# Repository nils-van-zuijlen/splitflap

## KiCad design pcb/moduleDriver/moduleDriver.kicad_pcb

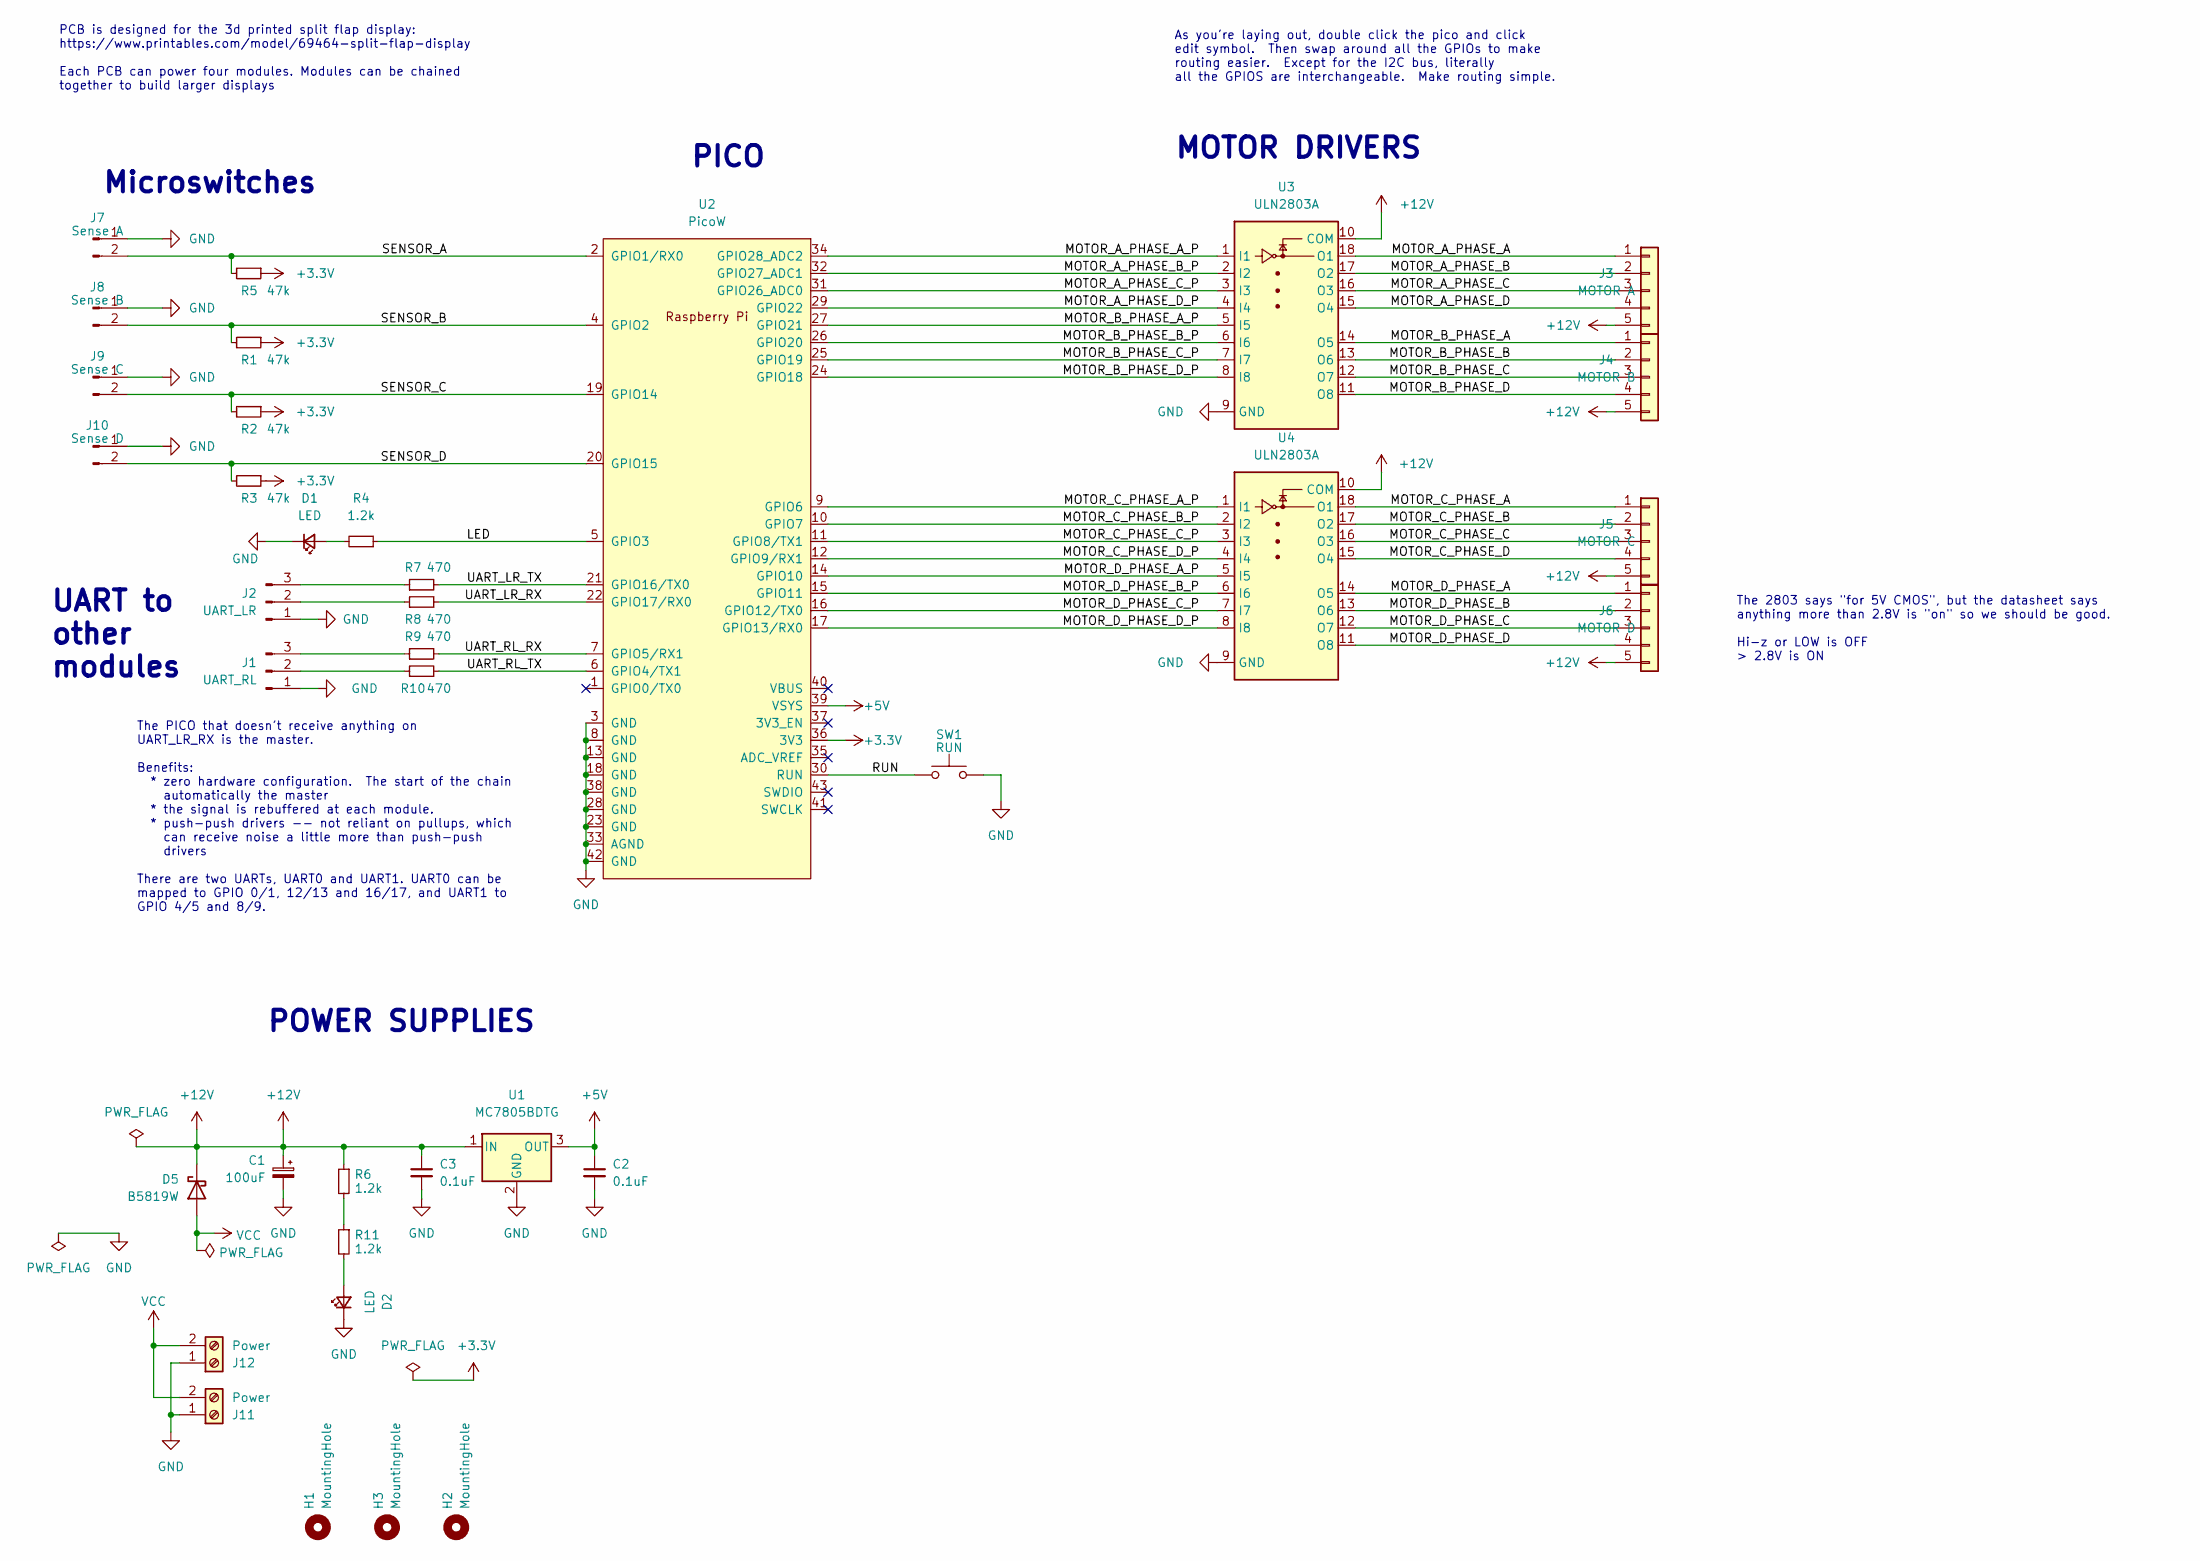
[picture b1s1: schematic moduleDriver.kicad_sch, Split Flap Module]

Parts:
C1: 100uF; CP_Elec_8x10; LCSC# C176665
C2, C3: 0.1uF; C_1206_3216Metric; LCSC# C14663
D1, D2: LED; LED_1206_3216Metric; LCSC# C72041
D5: B5819W; D_SOD-123; LCSC# C8598
H1, H2, H3: MountingHole; MountingHole_3.2mm_M3_ISO7380
J1: UART_RL; JST_XH_B3B-XH-A_1x03_P2.50mm_Vertical
J2: UART_LR; JST_XH_B3B-XH-A_1x03_P2.50mm_Vertical
J3: MOTOR A; JST_XH_B5B-XH-A_1x05_P2.50mm_Vertical
J4: MOTOR B; JST_XH_B5B-XH-A_1x05_P2.50mm_Vertical
J5: MOTOR C; JST_XH_B5B-XH-A_1x05_P2.50mm_Vertical
J6: MOTOR D; JST_XH_B5B-XH-A_1x05_P2.50mm_Vertical
J7: Sense A; JST_XH_B2B-XH-A_1x02_P2.50mm_Vertical
J8: Sense B; JST_XH_B2B-XH-A_1x02_P2.50mm_Vertical
J9: Sense C; JST_XH_B2B-XH-A_1x02_P2.50mm_Vertical
J10: Sense D; JST_XH_B2B-XH-A_1x02_P2.50mm_Vertical
J11, J12: Power; PhoenixContact_MSTBA_2,5_2-G_1x02_P5.00mm_Horizontal
R1, R2, R3, R5: 47k; R_1206_3216Metric; LCSC# C25819
R4, R6, R11: 1.2k; R_1206_3216Metric; LCSC# C22765
R7, R8, R9, R10: 470; R_1206_3216Metric; LCSC# C23179
SW1: RUN; SW_PUSH_6mm
U1: MC7805BDTG; TO-252-2; LCSC# C83632
U2: PicoW; RPi_PicoW_SMD_TH
U3, U4: ULN2803A; DIP-18_W7.62mm_Socket; LCSC# C181731

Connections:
+3.3V: R1.1, R2.1, R3.1, R5.1, U2.36 (3V3)
+5V: C2.1, U1.3 (OUT), U2.39 (VSYS)
+12V: C1.1, C3.1, D5.1 (K), J3.5, J4.5, J5.5, J6.5, R6.1, U1.1 (IN), U3.10 (COM), U4.10 (COM)
/LED: R4.1, U2.5 (GPIO3)
/MOTOR_A_PHASE_A: J3.1, U3.18 (O1)
/MOTOR_A_PHASE_A_P: U2.34 (GPIO28_ADC2), U3.1 (I1)
/MOTOR_A_PHASE_B: J3.2, U3.17 (O2)
/MOTOR_A_PHASE_B_P: U2.32 (GPIO27_ADC1), U3.2 (I2)
/MOTOR_A_PHASE_C: J3.3, U3.16 (O3)
/MOTOR_A_PHASE_C_P: U2.31 (GPIO26_ADC0), U3.3 (I3)
/MOTOR_A_PHASE_D: J3.4, U3.15 (O4)
/MOTOR_A_PHASE_D_P: U2.29 (GPIO22), U3.4 (I4)
/MOTOR_B_PHASE_A: J4.1, U3.14 (O5)
/MOTOR_B_PHASE_A_P: U2.27 (GPIO21), U3.5 (I5)
/MOTOR_B_PHASE_B: J4.2, U3.13 (O6)
/MOTOR_B_PHASE_B_P: U2.26 (GPIO20), U3.6 (I6)
/MOTOR_B_PHASE_C: J4.3, U3.12 (O7)
/MOTOR_B_PHASE_C_P: U2.25 (GPIO19), U3.7 (I7)
/MOTOR_B_PHASE_D: J4.4, U3.11 (O8)
/MOTOR_B_PHASE_D_P: U2.24 (GPIO18), U3.8 (I8)
/MOTOR_C_PHASE_A: J5.1, U4.18 (O1)
/MOTOR_C_PHASE_A_P: U2.9 (GPIO6), U4.1 (I1)
/MOTOR_C_PHASE_B: J5.2, U4.17 (O2)
/MOTOR_C_PHASE_B_P: U2.10 (GPIO7), U4.2 (I2)
/MOTOR_C_PHASE_C: J5.3, U4.16 (O3)
/MOTOR_C_PHASE_C_P: U2.11 (GPIO8/TX1), U4.3 (I3)
/MOTOR_C_PHASE_D: J5.4, U4.15 (O4)
/MOTOR_C_PHASE_D_P: U2.12 (GPIO9/RX1), U4.4 (I4)
/MOTOR_D_PHASE_A: J6.1, U4.14 (O5)
/MOTOR_D_PHASE_A_P: U2.14 (GPIO10), U4.5 (I5)
/MOTOR_D_PHASE_B: J6.2, U4.13 (O6)
/MOTOR_D_PHASE_B_P: U2.15 (GPIO11), U4.6 (I6)
/MOTOR_D_PHASE_C: J6.3, U4.12 (O7)
/MOTOR_D_PHASE_C_P: U2.16 (GPIO12/TX0), U4.7 (I7)
/MOTOR_D_PHASE_D: J6.4, U4.11 (O8)
/MOTOR_D_PHASE_D_P: U2.17 (GPIO13/RX0), U4.8 (I8)
/RUN: SW1.1, U2.30 (RUN)
/SENSOR_A: J7.2, R5.2, U2.2 (GPIO1/RX0)
/SENSOR_B: J8.2, R1.2, U2.4 (GPIO2)
/SENSOR_C: J9.2, R2.2, U2.19 (GPIO14)
/SENSOR_D: J10.2, R3.2, U2.20 (GPIO15)
/UART_LR_RX: R8.2, U2.22 (GPIO17/RX0)
/UART_LR_TX: R7.2, U2.21 (GPIO16/TX0)
/UART_RL_RX: R9.2, U2.7 (GPIO5/RX1)
/UART_RL_TX: R10.2, U2.6 (GPIO4/TX1)
GND: C1.2, C2.2, C3.2, D1.1 (K), D2.1 (K), J1.1, J2.1, J7.1, J8.1, J9.1, J10.1, J11.1, J12.1, SW1.2, U1.2 (GND), U2.3 (GND), U2.8 (GND), U2.13 (GND), U2.18 (GND), U2.23 (GND), U2.28 (GND), U2.33 (AGND), U2.38 (GND), U2.42 (GND), U3.9 (GND), U4.9 (GND)
unnamed: D1.2 (A), R4.2
unnamed: D2.2 (A), R11.2
unnamed: J1.2, R10.1
unnamed: J1.3, R9.1
unnamed: J2.2, R8.1
unnamed: J2.3, R7.1
unnamed: R6.2, R11.1
VCC: D5.2 (A), J11.2, J12.2

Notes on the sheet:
The 2803 says "for 5V CMOS", but the datasheet says anything more than 2.8V is "on" so we should be good. Hi-z or LOW is OFF > 2.8V is ON
Microswitches
UART to other modules
MOTOR DRIVERS
PICO
As you're laying out, double click the pico and click edit symbol. Then swap around all the GPIOs to make routing easier. Except for the I2C bus, literally all the GPIOS are interchangeable. Make routing simple.
PCB is designed for the 3d printed split flap display: https://www.printables.com/model/69464-split-flap-display Each PCB can power four modules. Modules can be chained together to build larger displays
POWER SUPPLIES
The PICO that doesn't receive anything on UART_LR_RX is the master. Benefits: * zero hardware configuration. The start of the chain automatically the master * the signal is rebuffered at each module. * push-push drivers -- not reliant on pullups, which can receive noise a little more than push-push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

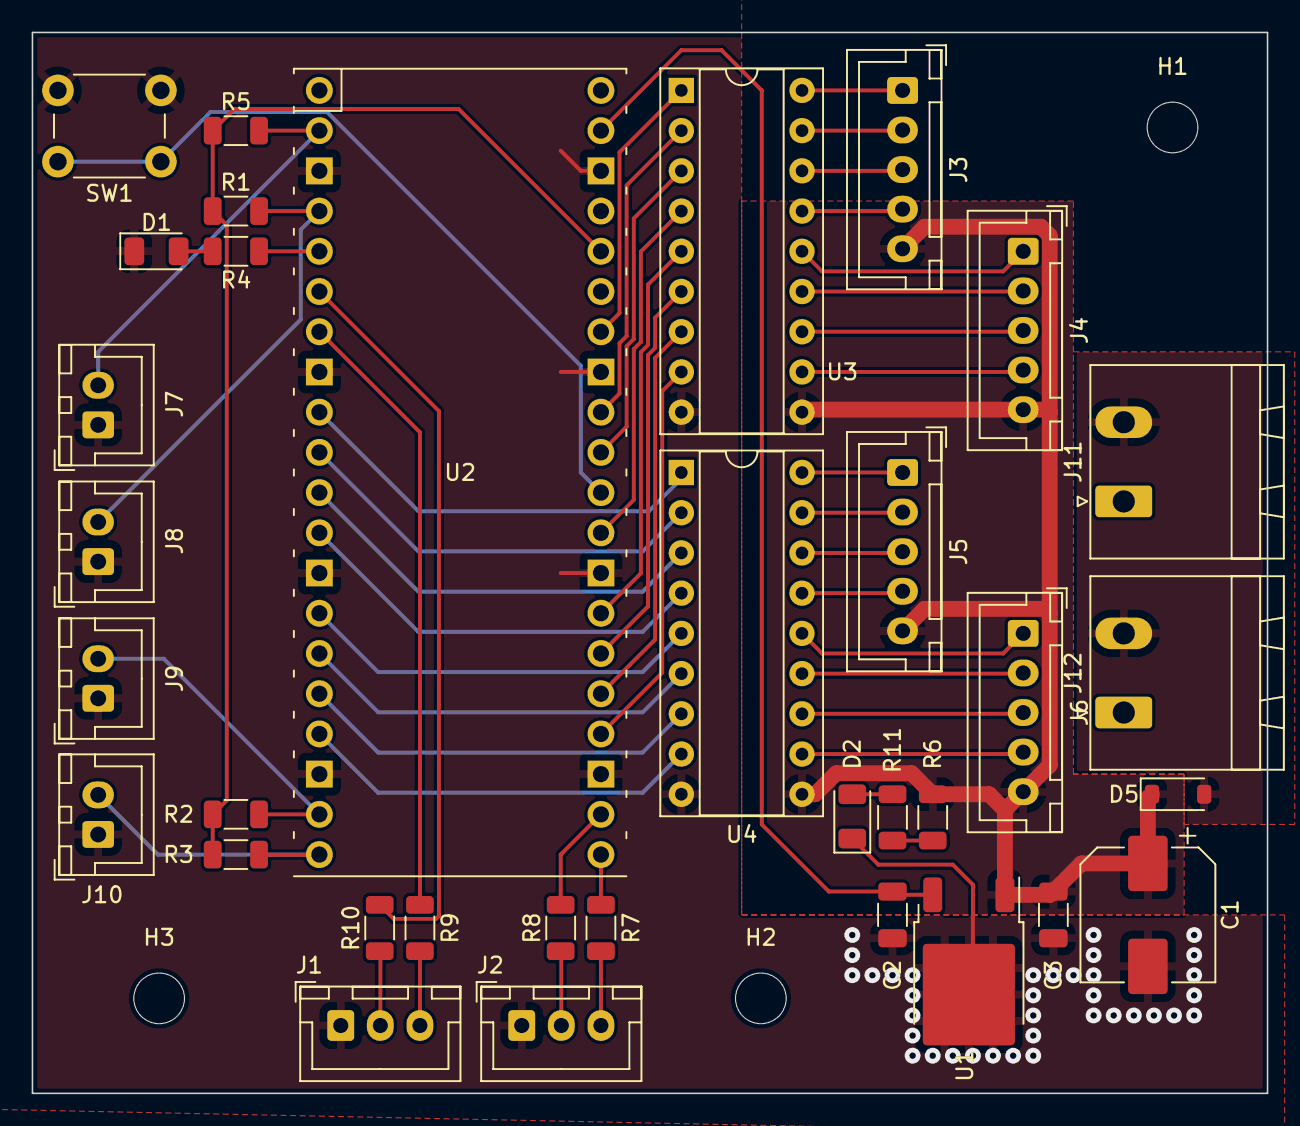
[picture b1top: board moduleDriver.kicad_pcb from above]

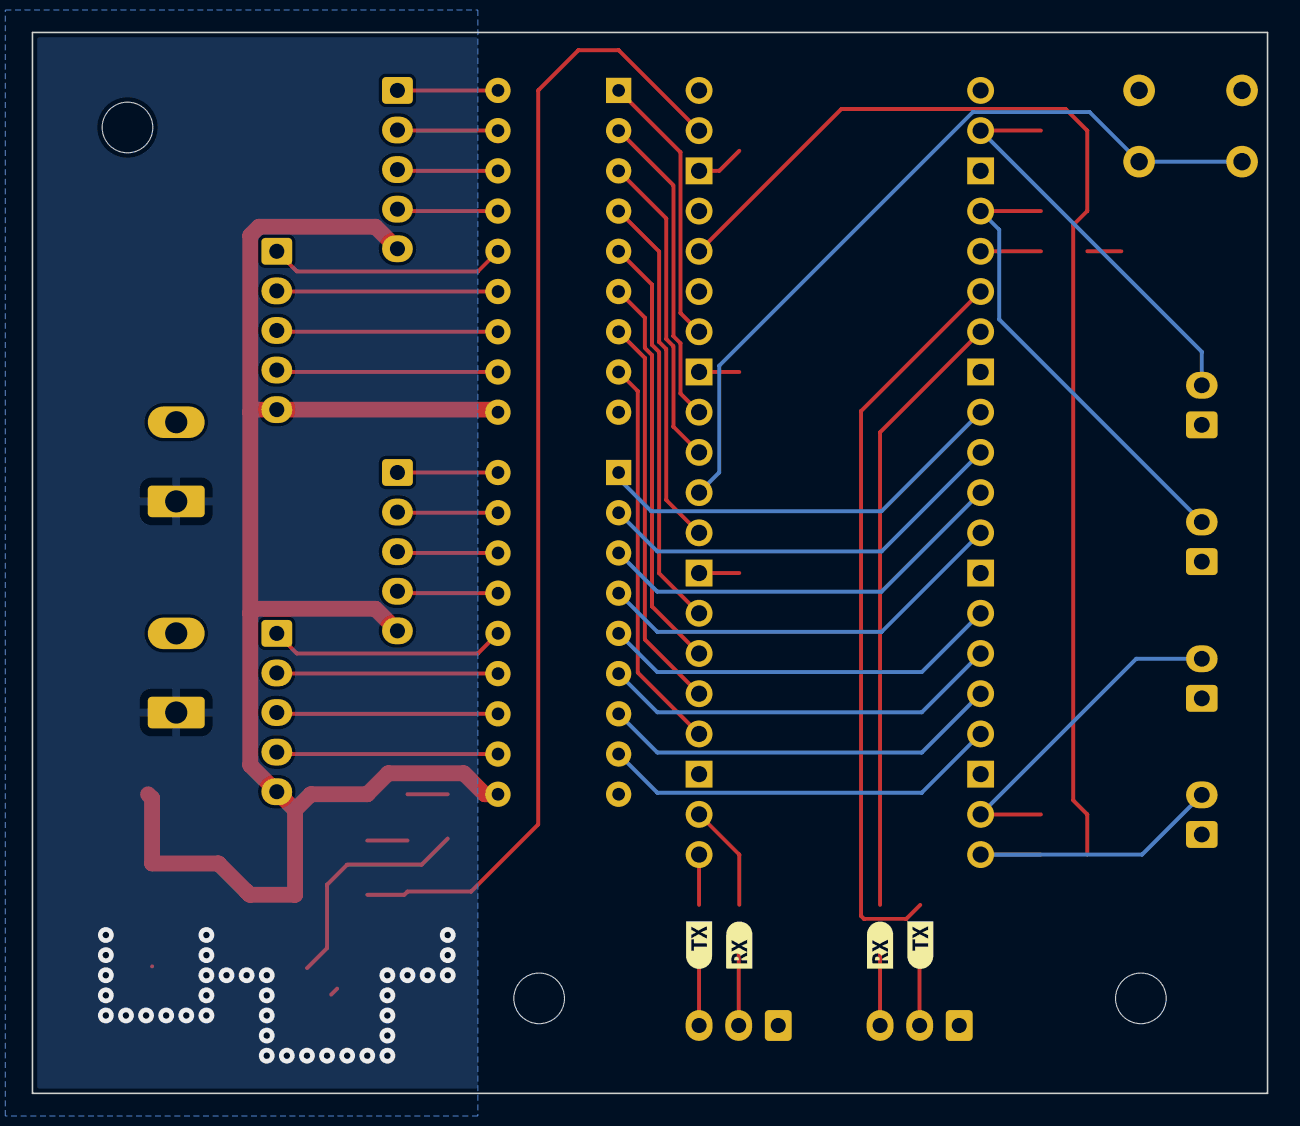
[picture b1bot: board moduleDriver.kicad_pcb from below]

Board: 2 copper layers, 78.0 x 67.0 mm, 41 parts (4 on the bottom side), 54 nets.

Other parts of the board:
kibuzzard-64922CB7, kibuzzard-64922CB7#2: G***; kibuzzard-64922CB7
kibuzzard-64922CEC, kibuzzard-64922CEC#2: G***; kibuzzard-64922CEC

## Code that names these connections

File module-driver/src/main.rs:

#![no_std]
#![no_main]

use rp_pico::entry;

use rp_pico::hal::multicore::{Multicore, Stack};
use rp_pico::hal::pac;
use rp_pico::hal::uart::{self, UartConfig, UartPeripheral};
use rp_pico::hal::{self, Clock};

use embedded_hal::prelude::*;
use embedded_hal::digital::v2::ToggleableOutputPin;
use fugit::{ExtU32, RateExtU32};
use panic_halt as _;

use usb_device::{class_prelude::*, prelude::*};
use usbd_serial::SerialPort;

mod module_logic;
mod motor_driver;
mod parser;

static mut CORE1_STACK: Stack<4096> = Stack::new();

fn core1_thread() -> ! {
    let mut pac = unsafe { pac::Peripherals::steal() };

    let mut sio = hal::Sio::new(pac.SIO);
    let pins = hal::gpio::Pins::new(
        pac.IO_BANK0,
        pac.PADS_BANK0,
        sio.gpio_bank0,
        &mut pac.RESETS,
    );

    sio.fifo.write_blocking(1);

    let timer = hal::Timer::new(pac.TIMER, &mut pac.RESETS);
    let mut count_down = timer.count_down();
    let mut delay = || {
        count_down.start(5.millis());
        let _ = nb::block!(count_down.wait());
    };

    // setup the rotor modules

    // module A
    let limit_sw = pins.gpio1.into_pull_up_input();
    let mut coil_a = pins.gpio28.into_push_pull_output();
    let mut coil_b = pins.gpio27.into_push_pull_output();
    let mut coil_c = pins.gpio26.into_push_pull_output();
    let mut coil_d = pins.gpio22.into_push_pull_output();

    let driver = motor_driver::MotorDriver::new(&mut coil_a, &mut coil_b, &mut coil_c, &mut coil_d);
    let mut module_a = module_logic::Module::new(driver, &limit_sw, 635);

    // module B
    let limit_sw = pins.gpio2.into_pull_up_input();
    let mut coil_a = pins.gpio21.into_push_pull_output();
    let mut coil_b = pins.gpio20.into_push_pull_output();
    let mut coil_c = pins.gpio19.into_push_pull_output();
    let mut coil_d = pins.gpio18.into_push_pull_output();

    let driver = motor_driver::MotorDriver::new(&mut coil_a, &mut coil_b, &mut coil_c, &mut coil_d);
    let mut module_b = module_logic::Module::new(driver, &limit_sw, 630);

    // module C
    let limit_sw = pins.gpio14.into_pull_up_input();
    let mut coil_a = pins.gpio6.into_push_pull_output();
    let mut coil_b = pins.gpio7.into_push_pull_output();
    let mut coil_c = pins.gpio8.into_push_pull_output();
    let mut coil_d = pins.gpio9.into_push_pull_output();

    let driver = motor_driver::MotorDriver::new(&mut coil_a, &mut coil_b, &mut coil_c, &mut coil_d);
    let mut module_c = module_logic::Module::new(driver, &limit_sw, 625);

    // module D
    let limit_sw = pins.gpio15.into_pull_up_input();
    let mut coil_a = pins.gpio10.into_push_pull_output();
    let mut coil_b = pins.gpio11.into_push_pull_output();
    let mut coil_c = pins.gpio12.into_push_pull_output();
    let mut coil_d = pins.gpio13.into_push_pull_output();

    let driver = motor_driver::MotorDriver::new(&mut coil_a, &mut coil_b, &mut coil_c, &mut coil_d);
    let mut module_d = module_logic::Module::new(driver, &limit_sw, 625);

    // reset barrels
    module_a.reset();
    module_b.reset();
    module_c.reset();
    module_d.reset();

    // status LED
    let mut led = pins
        .gpio3
        .into_push_pull_output_in_state(hal::gpio::PinState::High);
    let mut status_changes: u32 = 0;

    loop {
        let modules = [&mut module_a, &mut module_b, &mut module_c, &mut module_d];

        // Each value in the FIFO contains the module index in the 16 MSB (with values 0b00, 0b01, 0b10, 0b11) and the letter index in the 8 LSB
        // Asking for flap 0xFF on the module will reset module immediately
        while let Some(command) = sio.fifo.read() {
            let module_index = (command >> 16) & 0b11;
            let letter_index: u8 = (command & 0xFF).try_into().unwrap();

            if letter_index == 0xFF {
                modules[module_index as usize].reset();
            } else {
                modules[module_index as usize].set_target(letter_index);
            }
        }

        for module in modules {
            module.move_to_target().unwrap();
        }
        delay();

        status_changes += 1;
        if status_changes % 16 == 0 {
            led.toggle().unwrap()
        }
    }
}


#[entry]
fn main() -> ! {
    let mut pac = pac::Peripherals::take().unwrap();

    let mut sio = hal::Sio::new(pac.SIO);

    // Set up the watchdog driver - needed by the clock setup code
    let mut watchdog = hal::Watchdog::new(pac.WATCHDOG);

    // Configure the clocks
    //
    // The default is to generate a 125 MHz system clock
    let clocks = hal::clocks::init_clocks_and_plls(
        rp_pico::XOSC_CRYSTAL_FREQ,
        pac.XOSC,
        pac.CLOCKS,
        pac.PLL_SYS,
        pac.PLL_USB,
        &mut pac.RESETS,
        &mut watchdog,
    )
    .ok()
    .unwrap();

    let pins = rp_pico::Pins::new(
        pac.IO_BANK0,
        pac.PADS_BANK0,
        sio.gpio_bank0,
        &mut pac.RESETS,
    );

    // Start core1_thread
    let mut mc = Multicore::new(&mut pac.PSM, &mut pac.PPB, &mut sio.fifo);
    let cores = mc.cores();
    let core1 = &mut cores[1];
    let _task = core1.spawn(unsafe { &mut CORE1_STACK.mem }, core1_thread);

    // Wait until core1 also has initialized the pins
    sio.fifo.read_blocking();

    // setup the HW UART buses
    let tx0 = pins.gpio16.into_mode();
    let rx0 = pins.gpio17.into_mode();

    let uart_lr = UartPeripheral::new(pac.UART0, (tx0, rx0), &mut pac.RESETS)
        .enable(
            UartConfig::new(9600.Hz(), uart::DataBits::Eight, None, uart::StopBits::One),
            clocks.peripheral_clock.freq(),
        )
        .unwrap();

    let tx1 = pins.gpio4.into_mode();
    let rx1 = pins.gpio5.into_mode();

    let uart_rl = UartPeripheral::new(pac.UART1, (tx1, rx1), &mut pac.RESETS)
        .enable(
            UartConfig::new(9600.Hz(), uart::DataBits::Eight, None, uart::StopBits::One),
            clocks.peripheral_clock.freq(),
        )
        .unwrap();

    let read_uart = uart_rl;
    let write_uart = uart_lr;

    // Set up the USB driver
    let usb_bus = UsbBusAllocator::new(hal::usb::UsbBus::new(
        pac.USBCTRL_REGS,
        pac.USBCTRL_DPRAM,
        clocks.usb_clock,
        true,
        &mut pac.RESETS,
    ));

    // Set up the USB Communications Class Device driver
    let mut usb_serial = SerialPort::new(&usb_bus);

    // Create a USB device with a fake VID and PID
    let mut usb_dev = UsbDeviceBuilder::new(&usb_bus, UsbVidPid(0x16c0, 0x27dd))
        .manufacturer("Fake company")
        .product("Split flap")
        .serial_number("TEST")
        .device_class(2) // from: https://www.usb.org/defined-class-codes
        .build();

    sio.fifo.write((0 << 16) + 0); // blank
    sio.fifo.write((1 << 16) + 0); // blank
    sio.fifo.write((2 << 16) + 0); // blank
    sio.fifo.write((3 << 16) + 0); // blank

    let mut parser = parser::Parser::new(sio.fifo, write_uart);

    loop {
        // Check for new data on the USB bus
        if usb_dev.poll(&mut [&mut usb_serial]) {
            let mut buf = [0u8; 64];
            match usb_serial.read(&mut buf) {
                Err(_e) => {
                    // Do nothing
                }
                Ok(0) => {
                    // Do nothing
                }
                Ok(count) => {
                    buf.iter().take(count)
                        .for_each(|b| parser.parse_char(*b));
                }
            }
        }


        // Check for new data on the receiving UART
        if read_uart.uart_is_readable() {
            let mut buf = [0u8; 64];
            match read_uart.read_raw(&mut buf) {
                Err(_) => {}
                Ok(0) => {}
                Ok(count) => {
                    buf.iter().take(count)
                        .for_each(|b| parser.parse_char(*b));
                }
            }
        }
    }
}

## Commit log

2024-06-09 Add devenv
2024-06-09 Single thread
2024-06-09 It's alive!!!
2024-06-09 Now with asynchronous reset
2024-06-09 Slow the reset down so that the switch has time to click
2024-06-09 Make UART transmission work
2024-06-09 Add test script
2024-06-09 Add control Pico code
